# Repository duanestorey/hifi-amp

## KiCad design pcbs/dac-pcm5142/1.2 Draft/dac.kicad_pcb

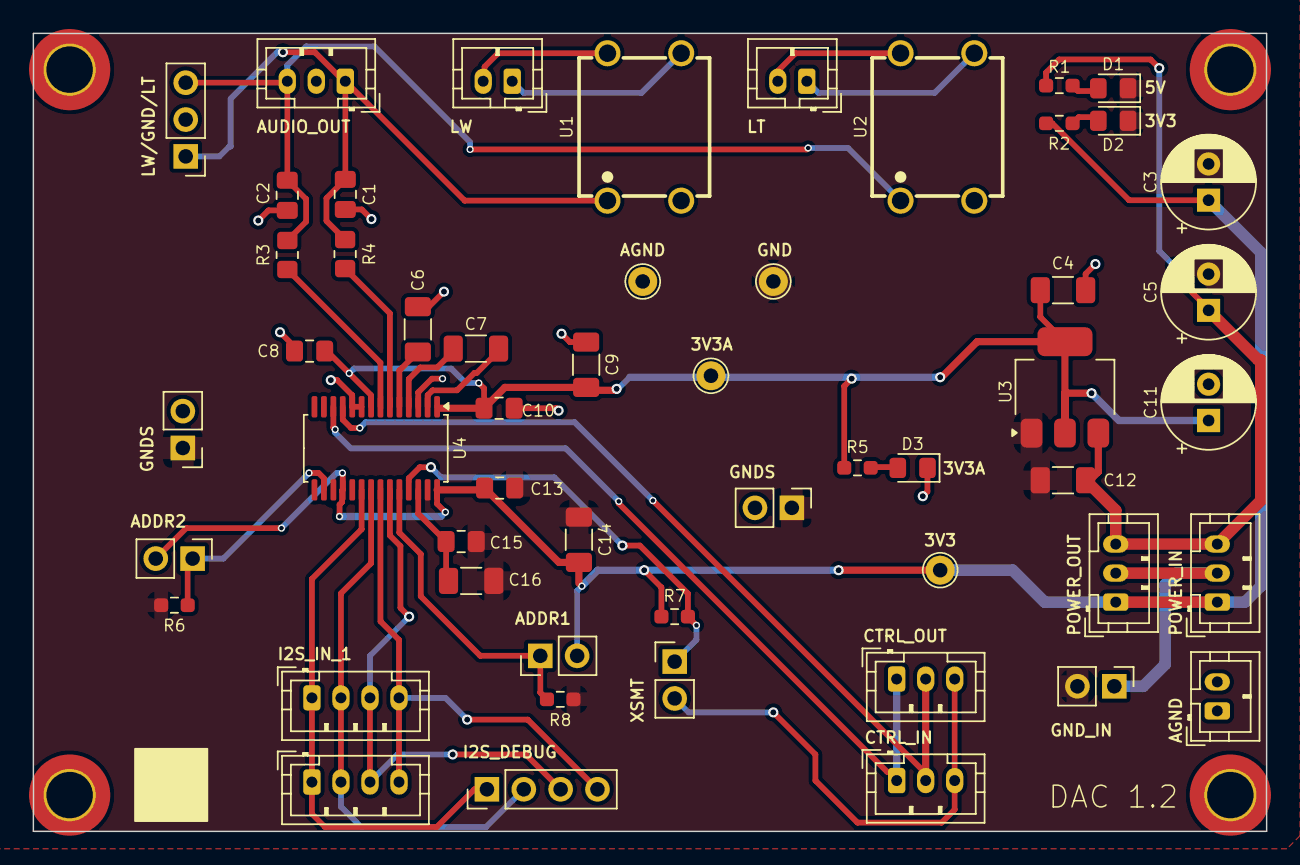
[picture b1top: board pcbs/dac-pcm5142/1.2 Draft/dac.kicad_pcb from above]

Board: 2 copper layers, 85.0 x 55.0 mm, 57 parts (0 on the bottom side), 31 nets.

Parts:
C1, C2: 2.2n 50V C0G; C_0805_2012Metric_Pad1.18x1.45mm_HandSolder
C3, C5, C11: 220u; CP_Radial_D6.3mm_P2.50mm
C4, C9, C12, C14, C16: 10U; C_1206_3216Metric_Pad1.33x1.80mm_HandSolder
C6, C7: 2.2u 25V; C_1206_3216Metric_Pad1.33x1.80mm_HandSolder
C8, C10, C13, C15: 0.1U; C_0805_2012Metric_Pad1.18x1.45mm_HandSolder
D1: RED; LED_0805_2012Metric_Pad1.15x1.40mm_HandSolder
D2, D3: BLUE; LED_0805_2012Metric_Pad1.15x1.40mm_HandSolder
H1, H2, H3, H4: MountingHole; MountingHole_3.2mm_M3_DIN965_Pad_TopOnly
J1, J7, J13, J15, J16: Conn_01x03_Pin; JST_PH_B3B-PH-K_1x03_P2.00mm_Vertical
J2, J3, J18: Conn_01x02_Pin; JST_PH_B2B-PH-K_1x02_P2.00mm_Vertical
J4: Conn_01x03_Pin; PinHeader_1x03_P2.54mm_Vertical
J5, J6, J8, J9, J10, J11: Conn_01x02_Pin; PinHeader_1x02_P2.54mm_Vertical
J12, J14: Conn_01x04_Pin; JST_PH_B4B-PH-K_1x04_P2.00mm_Vertical
J17: Conn_01x04_Pin; PinHeader_1x04_P2.54mm_Vertical
R1: 1.3K; R_0603_1608Metric_Pad0.98x0.95mm_HandSolder
R2, R5: 150R; R_0603_1608Metric_Pad0.98x0.95mm_HandSolder
R3, R4: 470R TF; R_0805_2012Metric_Pad1.20x1.40mm_HandSolder
R6, R7, R8: 4.7K; R_0603_1608Metric_Pad0.98x0.95mm_HandSolder
TP1, TP2, TP3, TP4: TestPoint; TestPoint_THTPad_D2.0mm_Drill1.0mm
U1, U2: DA101C_C6931652; XFMR-TH_4P-L9.5-W9.0-P5.08-LS10.2_C9900096976
U3: ZLDO1117QG33TA; SOT-223-3_TabPin2
U4: PCM5122PW; TSSOP-28_4.4x9.7mm_P0.65mm

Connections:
3V3: C3.1, C13.1, C14.1, J6.2, J7.1, J8.2, J13.1, R2.1, R7.1, TP4.1, U4.18 (MODE2/MS), U4.28 (DVDD)
3V3A: C4.1, C8.1, C9.1, C10.1, C11.1, R5.1, TP3.1, U3.2 (VO), U4.1 (CPVDD), U4.8 (AVDD)
5V: C5.1, C12.1, J7.3, J13.3, R1.1, U3.3 (VI)
ADDR1: J8.1, R8.2, U4.24 (ADR1/MISO/FMT)
ADDR2: J6.1, R6.2, U4.16 (ADR2/GPIO2/DOUT)
AGND: C1.1, C2.1, C4.2, C6.1, C8.2, C9.2, C10.2, C11.2, D3.1 (K), J1.2, J4.2, J5.2, J10.2, J18.1, J18.2, TP1.1, U1.3, U2.3, U4.3 (CPGND), U4.9 (AGND), U4.10 (VCOM/DEMP)
BCLK: J12.2, J14.2, J17.2, U4.21 (BCK)
DATA: J12.4, J14.4, J17.4, U4.22 (DIN)
GND: C3.2, C5.2, C12.2, C13.2, C14.2, C15.1, C16.2, D1.1 (K), D2.1 (K), J5.1, J10.1, J11.2, R6.1, R8.1, TP2.1, U3.1 (GND), U4.17 (MODE1), U4.27 (DGND)
GND_IN: J7.2, J11.1, J13.2
LEFT_TWEETER: C2.2, J1.3, J4.3, R3.2, U2.1
LEFT_WOOFER: C1.2, J1.1, J4.1, R4.2, U1.1
LRCLK: J12.3, J14.3, J17.3, U4.23 (LRCK)
LT_OUT_PRE: R3.1, U4.7 (OUTR)
LW_OUT_PRE: R4.1, U4.6 (OUTL)
unnamed: D1.2 (A), R1.2
unnamed: D2.2 (A), R2.2
unnamed: D3.2 (A), R5.2
unnamed: C7.2, U4.4 (CAPM)
unnamed: C7.1, U4.2 (CAPP)
unnamed: C15.2, C16.1, U4.26 (LDOO)
unnamed: C6.2, U4.5 (VNEG)
SCL: J15.1, J16.1, U4.12 (SCL/MC/ATT1)
SCLK: J12.1, J14.1, J17.1, U4.20 (SCK)
SDA: J15.2, J16.2, U4.11 (SDA/MOSI/ATT2)
SWL_NEG: J2.1, U1.4
SWL_OUT: J2.2, U1.6
SWR_NEG: J3.1, U2.4
SWR_OUT: J3.2, U2.6
XSMT: J9.1, R7.2, U4.25 (XSMT)
XSMT_IN: J9.2, J15.3, J16.3

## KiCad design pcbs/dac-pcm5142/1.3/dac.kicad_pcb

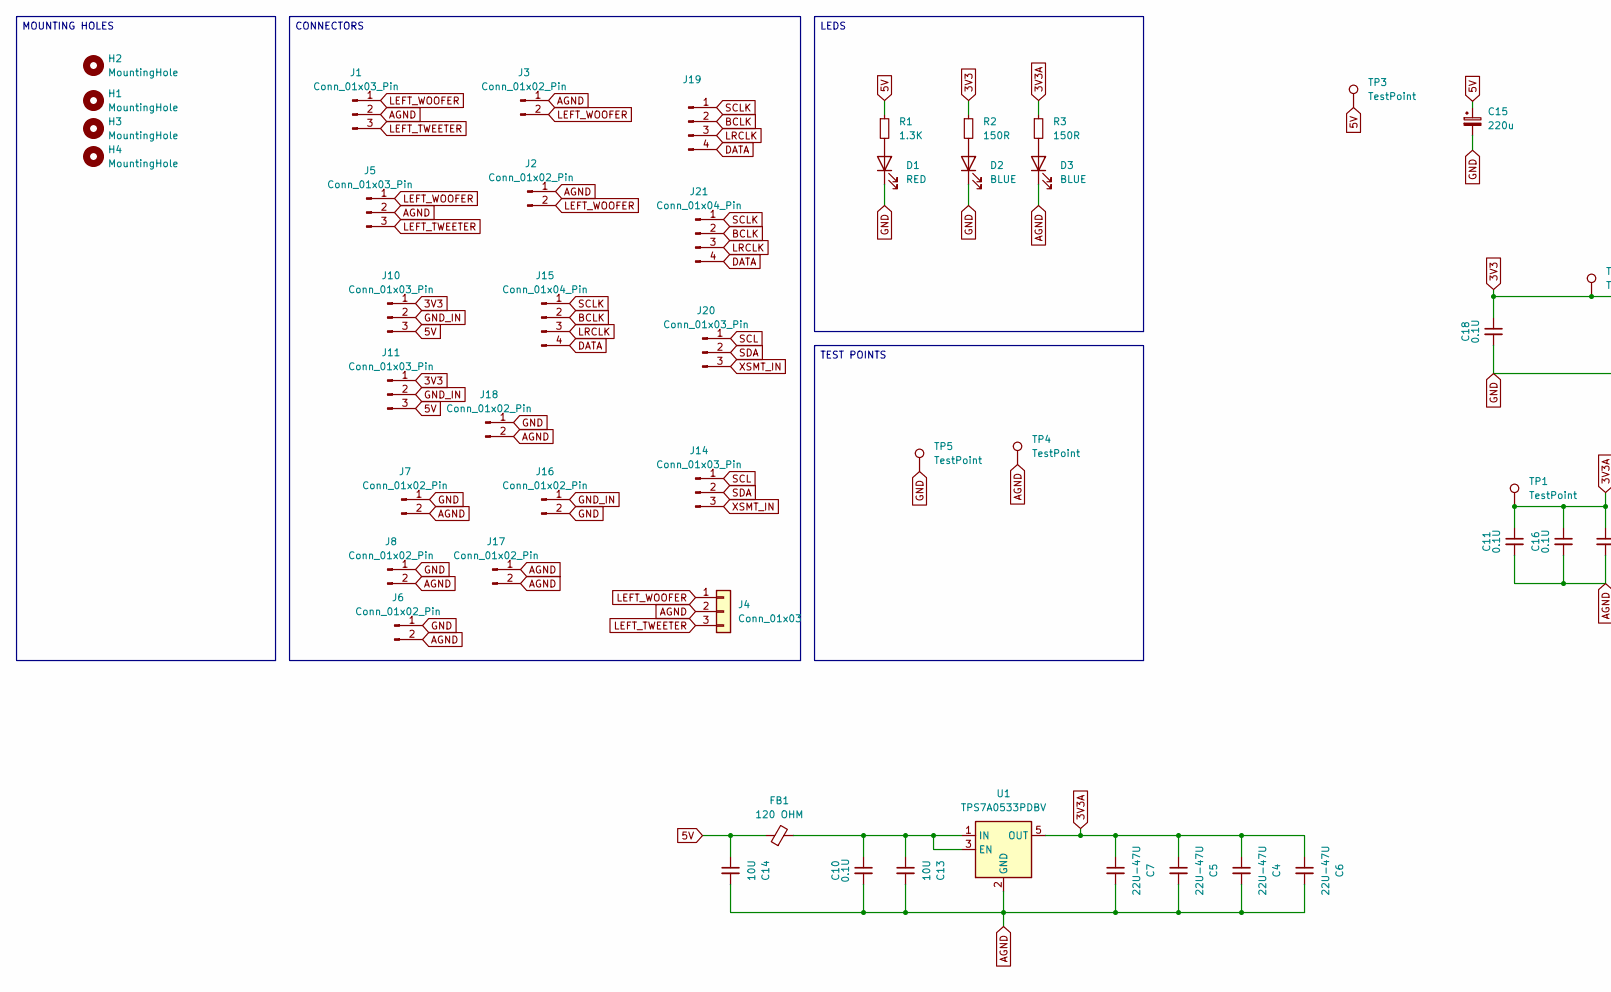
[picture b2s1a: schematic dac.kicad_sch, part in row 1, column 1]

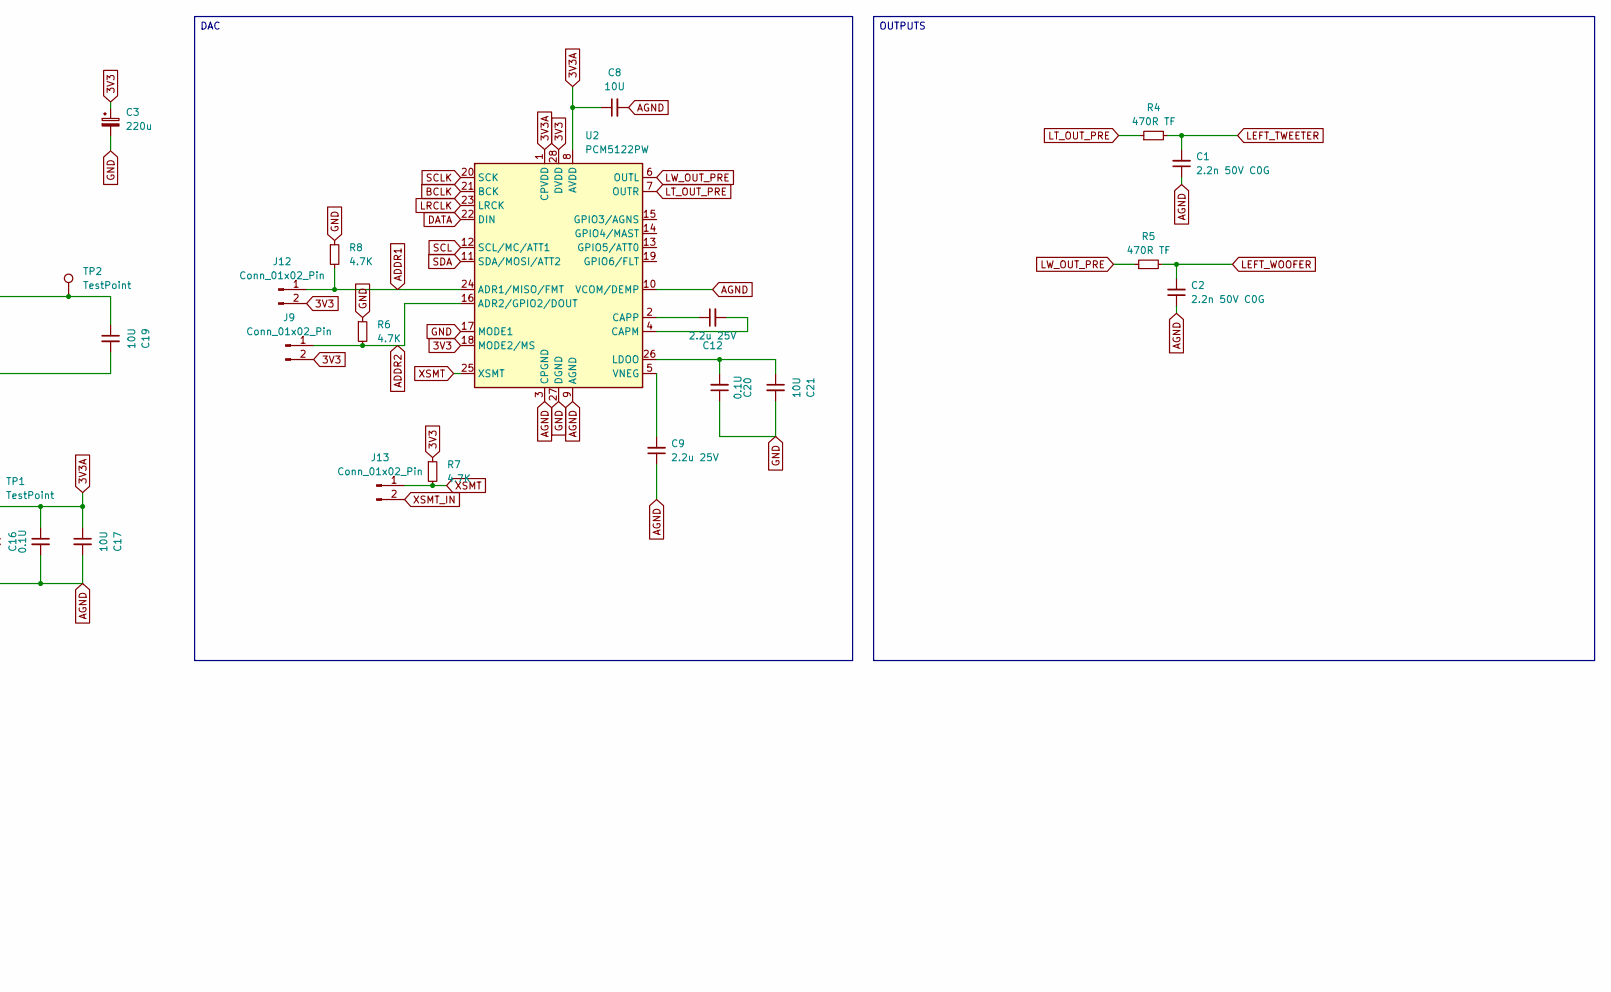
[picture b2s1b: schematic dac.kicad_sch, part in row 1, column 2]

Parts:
C1, C2: 2.2n 50V C0G; C_0805_2012Metric_Pad1.18x1.45mm_HandSolder; Mouser 791-0805N222G500CT
C3, C15: 220u; CP_Radial_D6.3mm_P2.50mm
C4, C5, C6, C7: 22U-47U; C_1206_3216Metric_Pad1.33x1.80mm_HandSolder
C8, C13, C14, C17, C19, C21: 10U; C_1206_3216Metric_Pad1.33x1.80mm_HandSolder
C9, C12: 2.2u 25V; C_1206_3216Metric_Pad1.33x1.80mm_HandSolder; Mouser 603-CC1206JKX78BB225
C10, C11, C16, C18, C20: 0.1U; C_0805_2012Metric_Pad1.18x1.45mm_HandSolder
D1: RED; LED_0805_2012Metric_Pad1.15x1.40mm_HandSolder
D2, D3: BLUE; LED_0805_2012Metric_Pad1.15x1.40mm_HandSolder
FB1: 120 OHM; R_0603_1608Metric_Pad0.98x0.95mm_HandSolder
H1, H2, H3, H4: MountingHole; MountingHole_3.2mm_M3_DIN965_Pad_TopOnly
J1, J10, J11, J14, J20: Conn_01x03_Pin; JST_PH_B3B-PH-K_1x03_P2.00mm_Vertical
J2, J3, J17: Conn_01x02_Pin; JST_PH_B2B-PH-K_1x02_P2.00mm_Vertical
J4: Conn_01x03; TerminalBlock_Phoenix_PT-1,5-3-3.5-H_1x03_P3.50mm_Horizontal
J5: Conn_01x03_Pin; PinHeader_1x03_P2.54mm_Vertical
J6, J7, J8, J9, J12, J13, J16, J18: Conn_01x02_Pin; PinHeader_1x02_P2.54mm_Vertical
J15, J19: Conn_01x04_Pin; JST_PH_B4B-PH-K_1x04_P2.00mm_Vertical
J21: Conn_01x04_Pin; PinHeader_1x04_P2.54mm_Vertical
R1: 1.3K; R_0603_1608Metric_Pad0.98x0.95mm_HandSolder
R2, R3: 150R; R_0603_1608Metric_Pad0.98x0.95mm_HandSolder
R4, R5: 470R TF; R_0805_2012Metric_Pad1.20x1.40mm_HandSolder; Mouser 603-RT0805FRE07470RL
R6, R7, R8: 4.7K; R_0603_1608Metric_Pad0.98x0.95mm_HandSolder
TP1, TP2, TP3, TP4, TP5: TestPoint; TestPoint_THTPad_D2.0mm_Drill1.0mm
U1: TPS7A0533PDBV; SOT-23-5
U2: PCM5122PW; TSSOP-28_4.4x9.7mm_P0.65mm; Mouser 595-PCM5122PWR

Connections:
3V3: C3.1, C18.1, C19.1, J9.2, J10.1, J11.1, J12.2, R2.1, R7.1, TP2.1, U2.18 (MODE2/MS), U2.28 (DVDD)
3V3A: C4.1, C5.1, C6.1, C7.1, C8.1, C11.1, C16.1, C17.1, R3.1, TP1.1, U1.5 (OUT), U2.1 (CPVDD), U2.8 (AVDD)
5V: C14.1, C15.1, FB1.1, J10.3, J11.3, R1.1, TP3.1
ADDR1: J12.1, R8.2, U2.24 (ADR1/MISO/FMT)
ADDR2: J9.1, R6.2, U2.16 (ADR2/GPIO2/DOUT)
AGND: C1.1, C2.1, C4.2, C5.2, C6.2, C7.2, C8.2, C9.1, C10.2, C11.2, C13.2, C14.2, C16.2, C17.2, D3.1 (K), J1.2, J2.1, J3.1, J4.2, J5.2, J6.2, J7.2, J8.2, J17.1, J17.2, J18.2, TP4.1, U1.2 (GND), U2.3 (CPGND), U2.9 (AGND), U2.10 (VCOM/DEMP)
BCLK: J15.2, J19.2, J21.2, U2.21 (BCK)
DATA: J15.4, J19.4, J21.4, U2.22 (DIN)
GND: C3.2, C15.2, C18.2, C19.2, C20.1, C21.2, D1.1 (K), D2.1 (K), J6.1, J7.1, J8.1, J16.2, J18.1, R6.1, R8.1, TP5.1, U2.17 (MODE1), U2.27 (DGND)
GND_IN: J10.2, J11.2, J16.1
LEFT_TWEETER: C1.2, J1.3, J4.3, J5.3, R4.2
LEFT_WOOFER: C2.2, J1.1, J2.2, J3.2, J4.1, J5.1, R5.2
LRCLK: J15.3, J19.3, J21.3, U2.23 (LRCK)
LT_OUT_PRE: R4.1, U2.7 (OUTR)
LW_OUT_PRE: R5.1, U2.6 (OUTL)
unnamed: D1.2 (A), R1.2
unnamed: D2.2 (A), R2.2
unnamed: D3.2 (A), R3.2
unnamed: C10.1, C13.1, FB1.2, U1.1 (IN), U1.3 (EN)
unnamed: C12.2, U2.4 (CAPM)
unnamed: C12.1, U2.2 (CAPP)
unnamed: C20.2, C21.1, U2.26 (LDOO)
unnamed: C9.2, U2.5 (VNEG)
SCL: J14.1, J20.1, U2.12 (SCL/MC/ATT1)
SCLK: J15.1, J19.1, J21.1, U2.20 (SCK)
SDA: J14.2, J20.2, U2.11 (SDA/MOSI/ATT2)
XSMT: J13.1, R7.2, U2.25 (XSMT)
XSMT_IN: J13.2, J14.3, J20.3

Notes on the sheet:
MOUNTING HOLES
TEST POINTS
CONNECTORS
OUTPUTS
DAC
LEDS

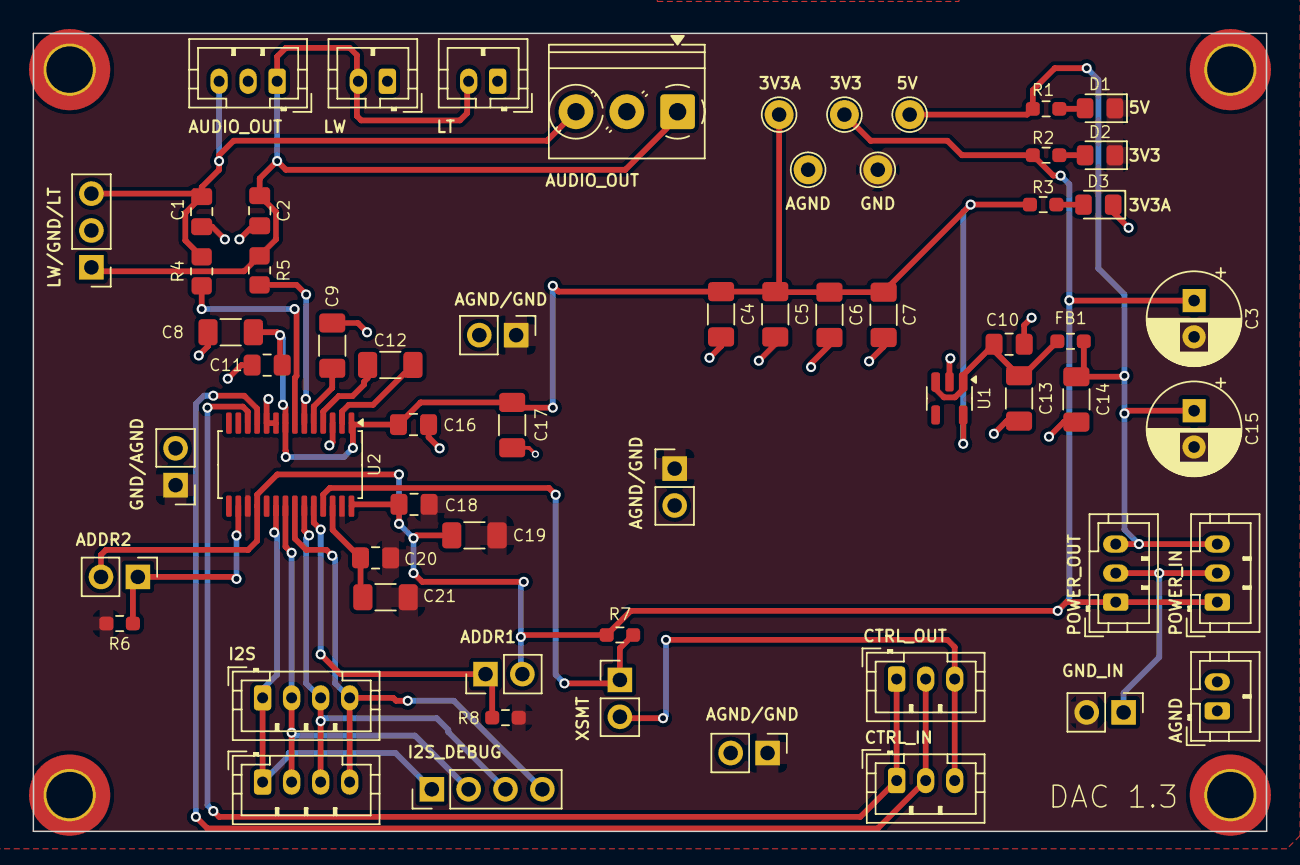
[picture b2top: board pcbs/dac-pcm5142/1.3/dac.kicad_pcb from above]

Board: 2 copper layers, 85.0 x 55.0 mm, 65 parts (0 on the bottom side), 28 nets.

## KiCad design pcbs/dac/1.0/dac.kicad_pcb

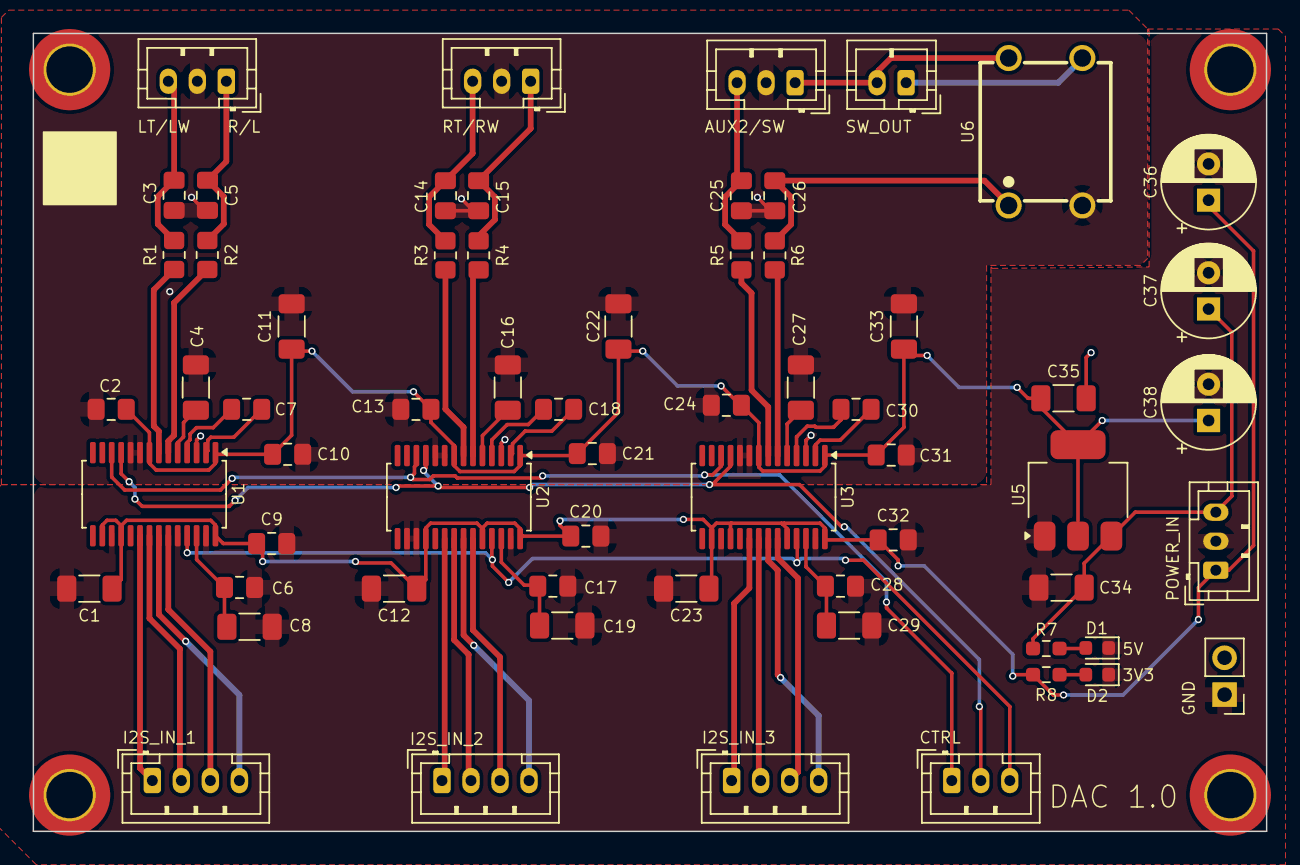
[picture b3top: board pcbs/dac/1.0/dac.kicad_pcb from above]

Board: 2 copper layers, 85.0 x 55.0 mm, 67 parts (0 on the bottom side), 48 nets.

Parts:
C1, C8, C11, C12, C19, C22, C23, C29, C33, C34, C35: 10U; C_1206_3216Metric_Pad1.33x1.80mm_HandSolder
C2, C6, C9, C10, C13, C17, C20, C21, C24, C28, C31, C32: 0.1U; C_0805_2012Metric_Pad1.18x1.45mm_HandSolder
C3, C5, C14, C15, C25, C26: 2.2n 50V C0G; C_0805_2012Metric_Pad1.18x1.45mm_HandSolder
C4, C16, C27: 2.2u 25V; C_1206_3216Metric_Pad1.33x1.80mm_HandSolder
C7, C18, C30: 2.2u 25V; C_0805_2012Metric_Pad1.18x1.45mm_HandSolder
C36, C37, C38: 220u; CP_Radial_D6.3mm_P2.50mm
D1: RED; LED_0603_1608Metric
D2: BLUE; LED_0603_1608Metric
H1, H2, H3, H4: MountingHole; MountingHole_3.2mm_M3_DIN965_Pad_TopOnly
J1, J3, J5: Conn_01x04_Pin; JST_PH_B4B-PH-K_1x04_P2.00mm_Vertical
J2, J4, J6, J8, J9: Conn_01x03_Pin; JST_PH_B3B-PH-K_1x03_P2.00mm_Vertical
J7: Conn_01x02_Pin; JST_PH_B2B-PH-K_1x02_P2.00mm_Vertical
J10: Conn_01x02_Pin; PinHeader_1x02_P2.54mm_Vertical
R1, R2, R3, R4, R5, R6: 470R TF; R_0805_2012Metric_Pad1.20x1.40mm_HandSolder
R7: 1.3K; R_0603_1608Metric_Pad0.98x0.95mm_HandSolder
R8: 150R; R_0603_1608Metric_Pad0.98x0.95mm_HandSolder
U1, U2, U3: PCM5122PW; TSSOP-28_4.4x9.7mm_P0.65mm
U5: ZLDO1117QG33TA; SOT-223-3_TabPin2
U6: DA101C_C6931652; XFMR-TH_4P-L9.5-W9.0-P5.08-LS10.2_C9900096976

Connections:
3V3: C1.1, C9.1, C12.1, C20.1, C23.1, C32.1, C36.1, J9.1, R8.1, U1.16 (ADR2/GPIO2/DOUT), U1.18 (MODE2/MS), U1.28 (DVDD), U2.18 (MODE2/MS), U2.24 (ADR1/MISO/FMT), U2.28 (DVDD), U3.16 (ADR2/GPIO2/DOUT), U3.18 (MODE2/MS), U3.24 (ADR1/MISO/FMT), U3.28 (DVDD)
3V3A: C2.1, C10.1, C11.1, C13.1, C21.1, C22.1, C24.1, C31.1, C33.1, C35.1, C38.1, U1.1 (CPVDD), U1.8 (AVDD), U2.1 (CPVDD), U2.8 (AVDD), U3.1 (CPVDD), U3.8 (AVDD), U5.2 (VO)
5V: C34.1, C37.1, J9.3, R7.1, U5.3 (VI)
AGND: C2.2, C3.1, C4.1, C5.1, C10.2, C11.2, C13.2, C14.1, C15.1, C16.1, C21.2, C22.2, C24.2, C25.1, C26.1, C27.1, C31.2, C33.2, C35.2, J2.2, J4.2, J6.2, J10.2, U1.3 (CPGND), U1.9 (AGND), U1.10 (VCOM/DEMP), U2.3 (CPGND), U2.9 (AGND), U2.10 (VCOM/DEMP), U3.3 (CPGND), U3.9 (AGND), U3.10 (VCOM/DEMP), U6.3
BCLK0: J1.2, U1.21 (BCK)
BCLK1: J3.2, U2.21 (BCK)
BCLK2: J5.2, U3.21 (BCK)
DATA0: J1.4, U1.22 (DIN)
DATA1: J3.4, U2.22 (DIN)
DATA2: J5.4, U3.22 (DIN)
GND: C1.2, C6.1, C8.2, C9.2, C12.2, C17.1, C19.2, C20.2, C23.2, C28.1, C29.2, C32.2, C34.2, C36.2, C37.2, C38.2, D1.1 (K), D2.1 (K), J9.2, J10.1, U1.17 (MODE1), U1.24 (ADR1/MISO/FMT), U1.27 (DGND), U2.16 (ADR2/GPIO2/DOUT), U2.17 (MODE1), U2.27 (DGND), U3.17 (MODE1), U3.27 (DGND), U5.1 (GND)
LEFT_TWEETER: C3.2, J2.3, R1.2
LEFT_WOOFER: C5.2, J2.1, R2.2
LRCLK0: J1.3, U1.23 (LRCK)
LRCLK1: J3.3, U2.23 (LRCK)
LRCLK2: J5.3, U3.23 (LRCK)
LT_OUT_PRE: R1.1, U1.7 (OUTR)
LW_OUT_PRE: R2.1, U1.6 (OUTL)
MCLK0: J1.1, U1.20 (SCK)
MCLK1: J3.1, U2.20 (SCK)
MCLK2: J5.1, U3.20 (SCK)
unnamed: D1.2 (A), R7.2
unnamed: D2.2 (A), R8.2
unnamed: C7.2, U1.4 (CAPM)
unnamed: C7.1, U1.2 (CAPP)
unnamed: C6.2, C8.1, U1.26 (LDOO)
unnamed: C4.2, U1.5 (VNEG)
unnamed: C18.2, U2.4 (CAPM)
unnamed: C18.1, U2.2 (CAPP)
unnamed: C17.2, C19.1, U2.26 (LDOO)
unnamed: C16.2, U2.5 (VNEG)
unnamed: C30.2, U3.4 (CAPM)
unnamed: C30.1, U3.2 (CAPP)
unnamed: C28.2, C29.1, U3.26 (LDOO)
unnamed: C27.2, U3.5 (VNEG)
RIGHT_TWEETER: C14.2, J4.3, R3.2
RIGHT_WOOFER: C15.2, J4.1, R4.2
RT_OUT_PRE: R3.1, U2.7 (OUTR)
RW_OUT_PRE: R4.1, U2.6 (OUTL)
SCL: J8.1, U1.12 (SCL/MC/ATT1), U2.12 (SCL/MC/ATT1), U3.12 (SCL/MC/ATT1)
SDA: J8.2, U1.11 (SDA/MOSI/ATT2), U2.11 (SDA/MOSI/ATT2), U3.11 (SDA/MOSI/ATT2)
SPARE_OUT: C25.2, J6.3, R5.2
SPARE_OUT_PRE: R5.1, U3.7 (OUTR)
SUBWOOFER: C26.2, R6.2, U6.1
SW_NEG: J7.1, U6.4
SW_OUT: J6.1, J7.2, U6.6
SW_OUT_PRE: R6.1, U3.6 (OUTL)
XSMT: J8.3, U1.25 (XSMT), U2.25 (XSMT), U3.25 (XSMT)

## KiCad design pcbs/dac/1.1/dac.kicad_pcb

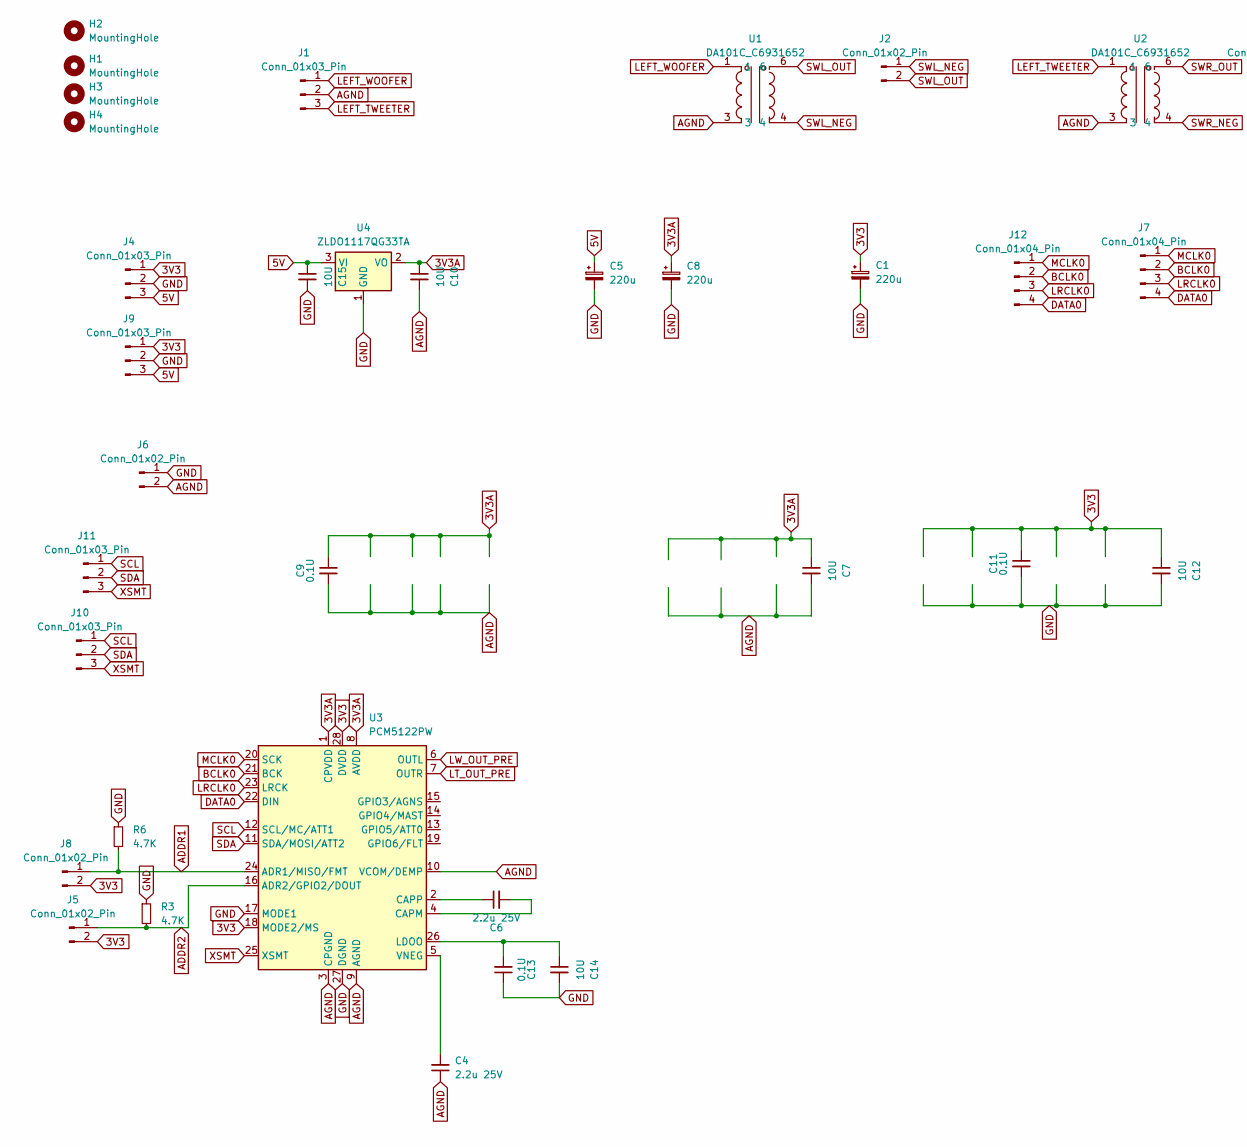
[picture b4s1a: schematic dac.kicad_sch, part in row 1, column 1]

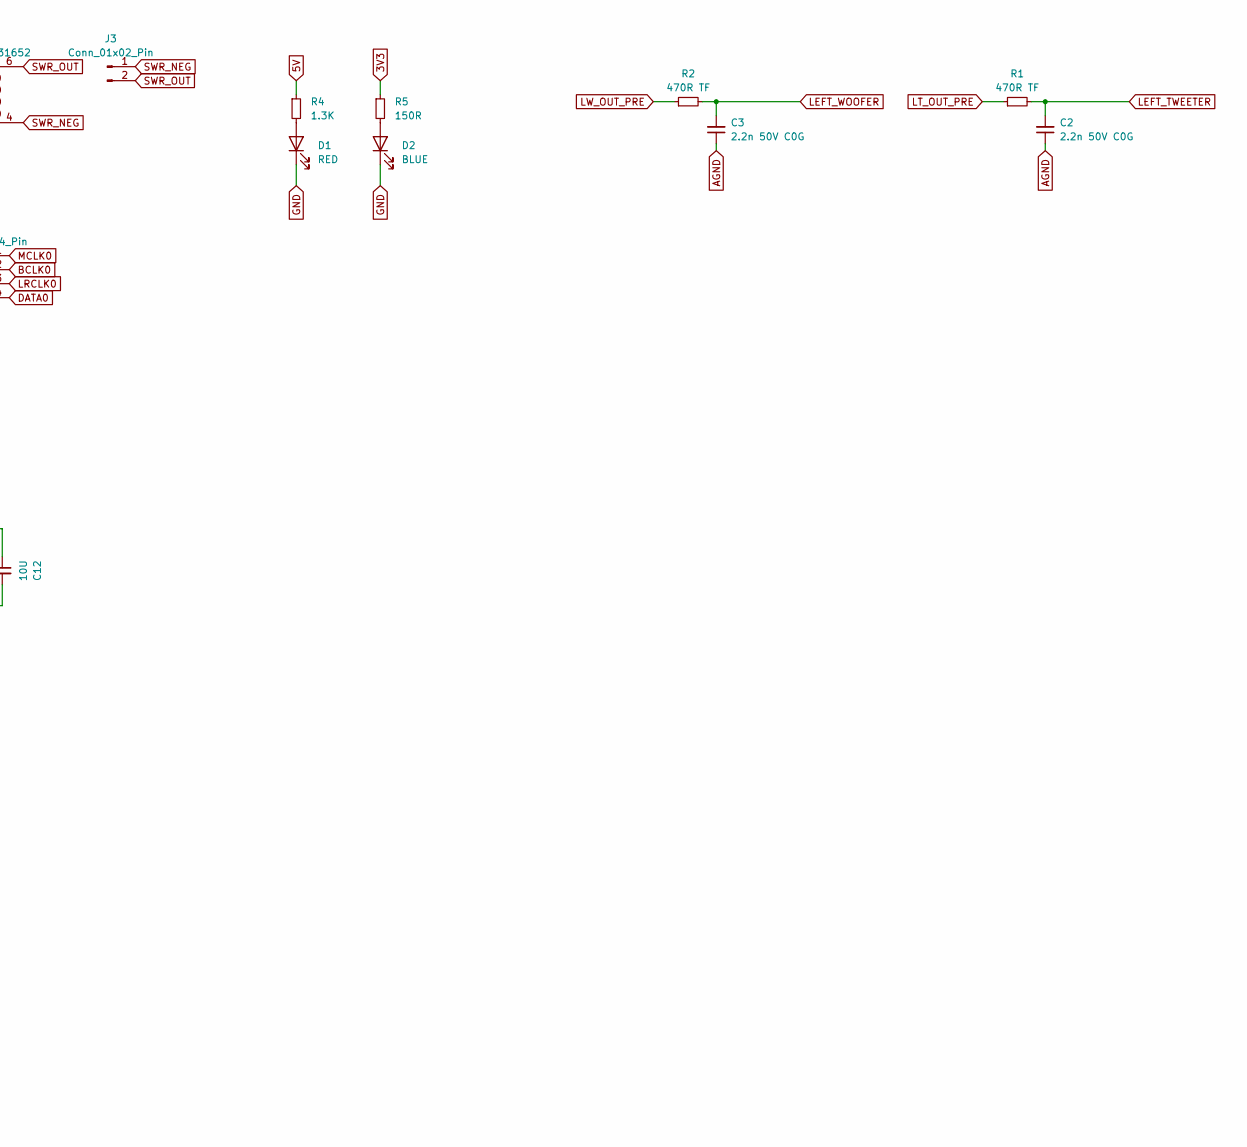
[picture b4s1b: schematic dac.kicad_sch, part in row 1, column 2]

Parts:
C1, C5, C8: 220u; CP_Radial_D6.3mm_P2.50mm
C2, C3: 2.2n 50V C0G; C_0805_2012Metric_Pad1.18x1.45mm_HandSolder; Mouser 791-0805N222F500CT
C4: 2.2u 25V; C_1206_3216Metric_Pad1.33x1.80mm_HandSolder; Mouser 603-CC1206JKX78BB225
C6: 2.2u 25V; C_0805_2012Metric_Pad1.18x1.45mm_HandSolder; Mouser 603-CC1206JKX78BB225
C7, C10, C12, C14, C15: 10U; C_1206_3216Metric_Pad1.33x1.80mm_HandSolder
C9, C11, C13: 0.1U; C_0805_2012Metric_Pad1.18x1.45mm_HandSolder
D1: RED; LED_0603_1608Metric
D2: BLUE; LED_0603_1608Metric
H1, H2, H3, H4: MountingHole; MountingHole_3.2mm_M3_DIN965_Pad_TopOnly
J1, J4, J9, J10, J11: Conn_01x03_Pin; JST_PH_B3B-PH-K_1x03_P2.00mm_Vertical
J2, J3: Conn_01x02_Pin; JST_PH_B2B-PH-K_1x02_P2.00mm_Vertical
J5, J6, J8: Conn_01x02_Pin; PinHeader_1x02_P2.54mm_Vertical
J7, J12: Conn_01x04_Pin; JST_PH_B4B-PH-K_1x04_P2.00mm_Vertical
R1, R2: 470R TF; R_0805_2012Metric_Pad1.20x1.40mm_HandSolder; Mouser 603-RT0805FRE07470RL
R3, R6: 4.7K; R_0603_1608Metric_Pad0.98x0.95mm_HandSolder
R4: 1.3K; R_0603_1608Metric_Pad0.98x0.95mm_HandSolder
R5: 150R; R_0603_1608Metric_Pad0.98x0.95mm_HandSolder
U1, U2: DA101C_C6931652; XFMR-TH_4P-L9.5-W9.0-P5.08-LS10.2_C9900096976; LCSC Part C6931652
U3: PCM5122PW; TSSOP-28_4.4x9.7mm_P0.65mm; Mouser 595-PCM5122PWR
U4: ZLDO1117QG33TA; SOT-223-3_TabPin2

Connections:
3V3: C1.1, C11.1, C12.1, J4.1, J5.2, J8.2, J9.1, R5.1, U3.18 (MODE2/MS), U3.28 (DVDD)
3V3A: C7.1, C8.1, C9.1, C10.1, U3.1 (CPVDD), U3.8 (AVDD), U4.2 (VO)
5V: C5.1, C15.1, J4.3, J9.3, R4.1, U4.3 (VI)
ADDR1: J8.1, R6.2, U3.24 (ADR1/MISO/FMT)
ADDR2: J5.1, R3.2, U3.16 (ADR2/GPIO2/DOUT)
AGND: C2.1, C3.1, C4.1, C7.2, C9.2, C10.2, J1.2, J6.2, U1.3, U2.3, U3.3 (CPGND), U3.9 (AGND), U3.10 (VCOM/DEMP)
BCLK0: J7.2, J12.2, U3.21 (BCK)
DATA0: J7.4, J12.4, U3.22 (DIN)
GND: C1.2, C5.2, C8.2, C11.2, C12.2, C13.1, C14.2, C15.2, D1.1 (K), D2.1 (K), J4.2, J6.1, J9.2, R3.1, R6.1, U3.17 (MODE1), U3.27 (DGND), U4.1 (GND)
LEFT_TWEETER: C2.2, J1.3, R1.2, U2.1
LEFT_WOOFER: C3.2, J1.1, R2.2, U1.1
LRCLK0: J7.3, J12.3, U3.23 (LRCK)
LT_OUT_PRE: R1.1, U3.7 (OUTR)
LW_OUT_PRE: R2.1, U3.6 (OUTL)
MCLK0: J7.1, J12.1, U3.20 (SCK)
unnamed: D1.2 (A), R4.2
unnamed: D2.2 (A), R5.2
unnamed: C6.2, U3.4 (CAPM)
unnamed: C6.1, U3.2 (CAPP)
unnamed: C13.2, C14.1, U3.26 (LDOO)
unnamed: C4.2, U3.5 (VNEG)
SCL: J10.1, J11.1, U3.12 (SCL/MC/ATT1)
SDA: J10.2, J11.2, U3.11 (SDA/MOSI/ATT2)
SWL_NEG: J2.1, U1.4
SWL_OUT: J2.2, U1.6
SWR_NEG: J3.1, U2.4
SWR_OUT: J3.2, U2.6
XSMT: J10.3, J11.3, U3.25 (XSMT)

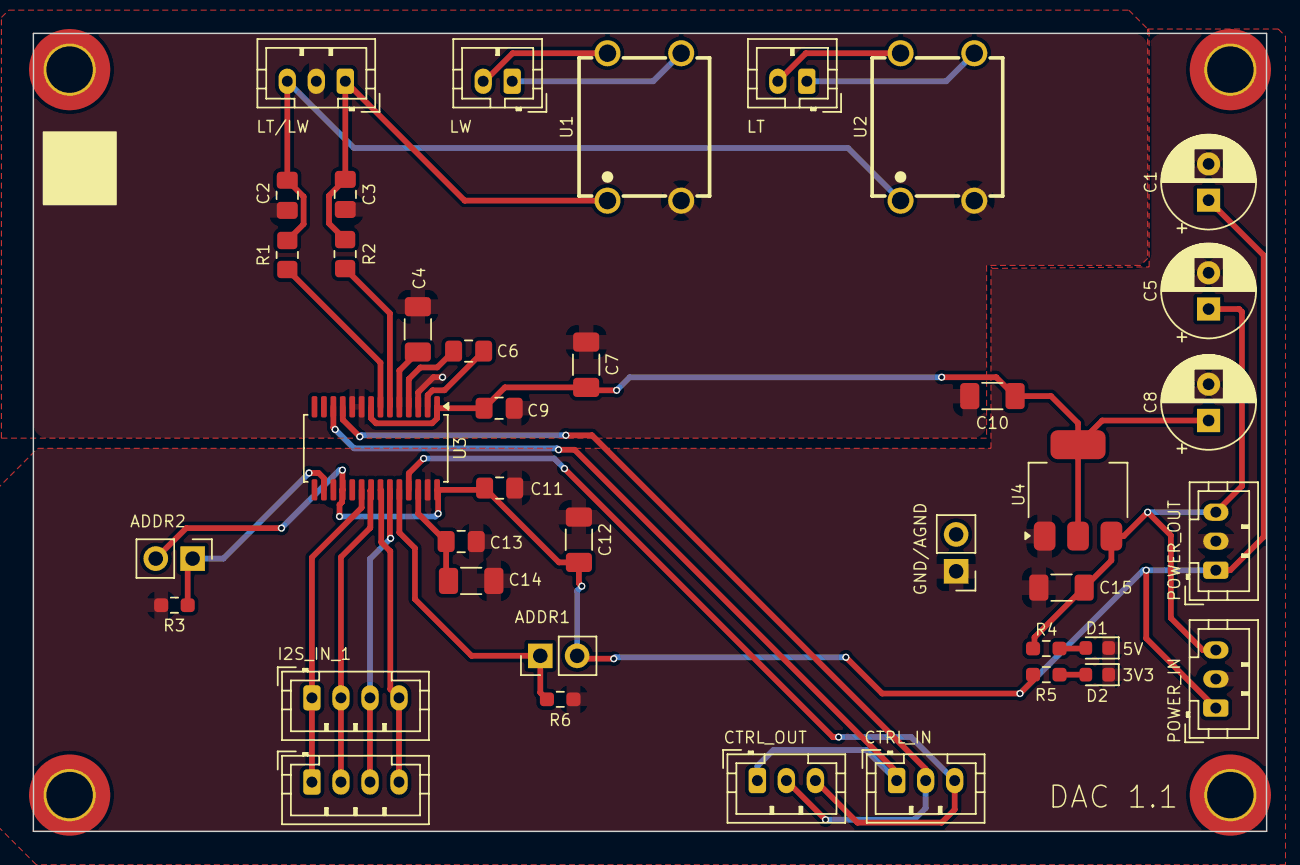
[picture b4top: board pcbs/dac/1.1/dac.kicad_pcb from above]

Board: 2 copper layers, 85.0 x 55.0 mm, 43 parts (0 on the bottom side), 28 nets.
